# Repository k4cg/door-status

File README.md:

# K4CG door-status

This program submits the k4cg space door status to "heimat". It is intended to run on an ESP8266 controller with micropython firmware. In the "hardware" directory, you can find a case design for OpenSCAD, which is suitable for 3D-printing.

[Link: Miropython ESP8266 Docs](http://docs.micropython.org/en/latest/esp8266/)

## Status Transmission

The data transfer is periodically performed by the ESP (~ 5 minute intervals) to http://heimat:8000 via PUT request.

It contains a JSON formatted structure like:
```
{"humidity": 35, "door": "open", "date": "2017-08-21 19:11:50", "tempDoor": 27}
```

## Code Upload

First time upload: Connect via serial port with mpfshell:

```
# mpfshell -c "open ttyUSB0"
mpfs [/]> put boot.py
mpfs [/]> put service.py
...
```

Update code:
```
# mpfshell -c "open ws:192.168.178.9,PASSWORD"
mpfs [/]> put boot.py
mpfs [/]> put service.py
...
mpfs [/]> repl
>>> reboot()
```

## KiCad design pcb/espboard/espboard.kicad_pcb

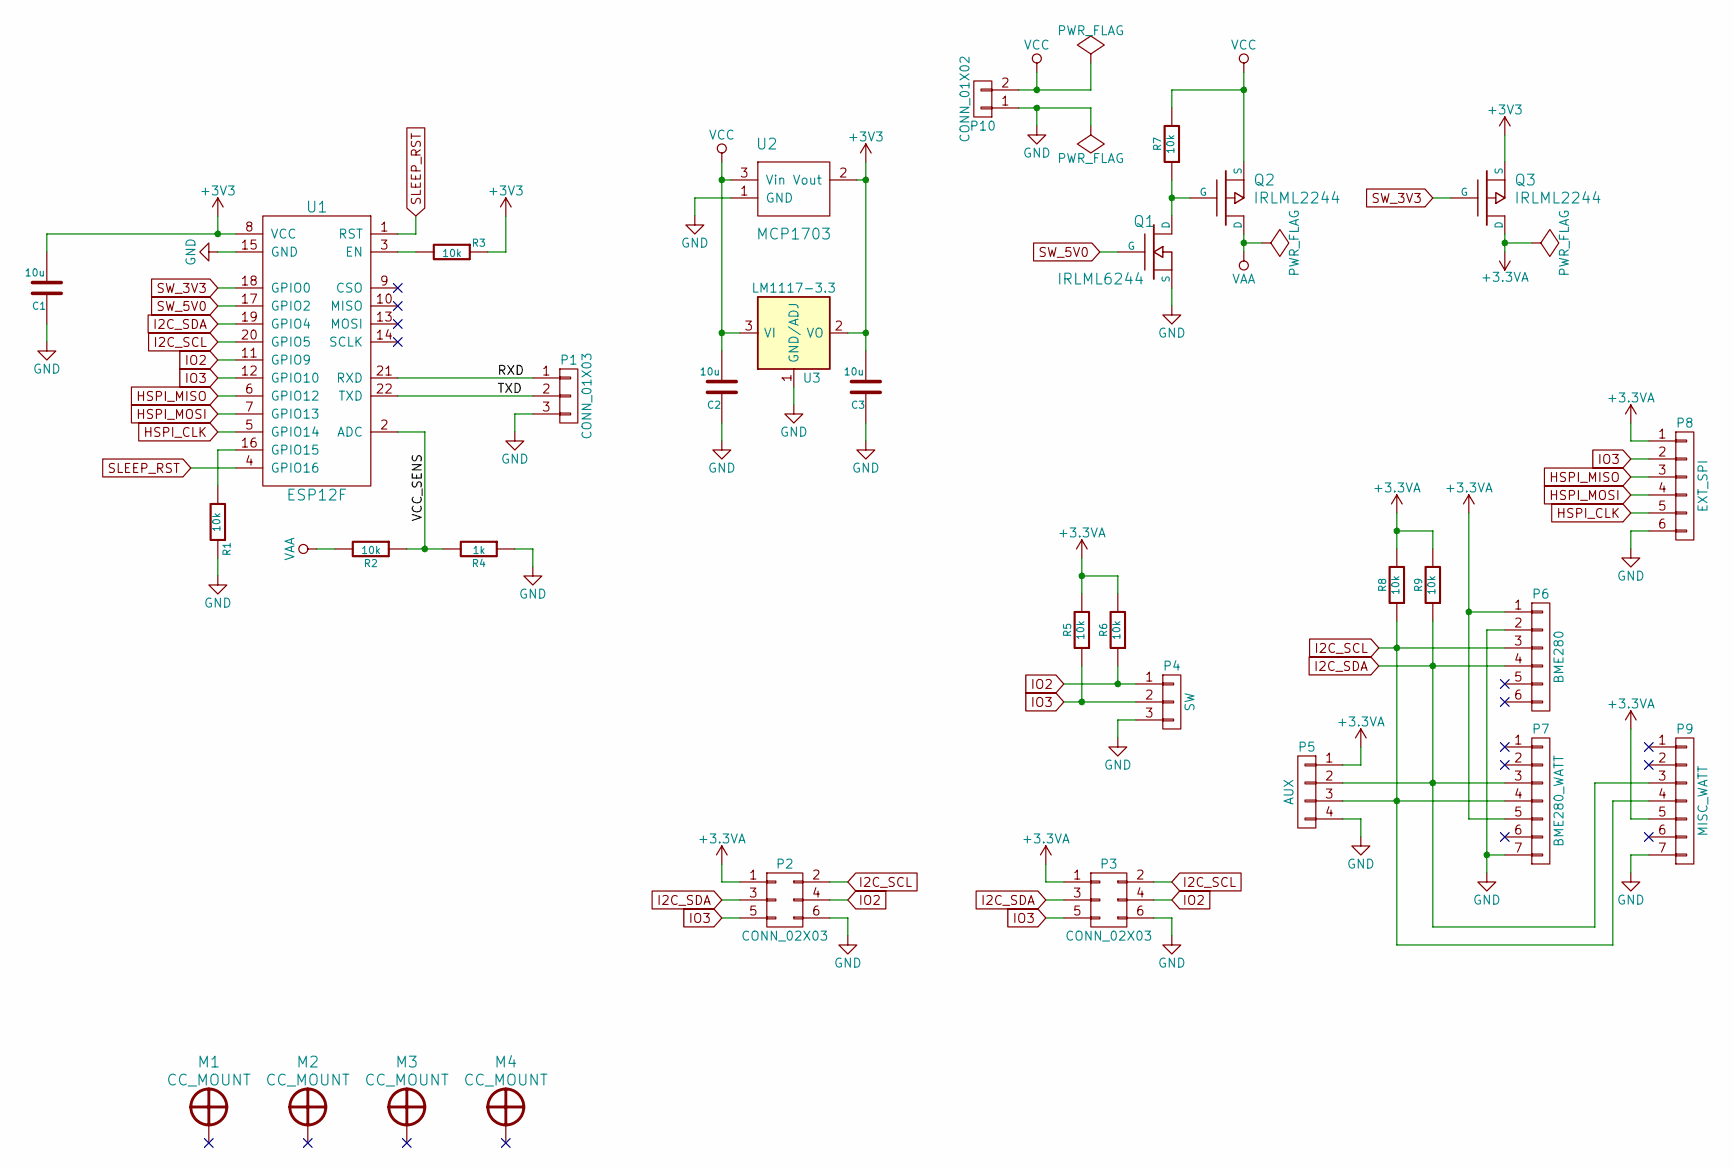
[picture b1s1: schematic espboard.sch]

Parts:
C1, C2, C3: 10u; rcl-cc-0402
M1, M2, M3, M4: CC_MOUNT; CC_MOUNT_PLATED_M3
P1: CONN_01X03; Pin_Header_Straight_1x03_Pitch2.54mm
P2, P3: CONN_02X03; con-harting-ml-ML6
P4: SW; Pin_Header_Straight_1x03_Pitch2.54mm
P5: AUX; Pin_Header_Straight_1x04_Pitch2.54mm
P6: BME280; Pin_Header_Straight_1x06_Pitch2.54mm
P7: BME280_WATT; Pin_Header_Straight_1x07_Pitch2.54mm
P8: EXT_SPI; Pin_Header_Straight_1x06_Pitch2.54mm
P9: MISC_WATT; Pin_Header_Straight_1x07_Pitch2.54mm
P10: CONN_01X02; Pin_Header_Straight_1x02_Pitch2.54mm
Q1: IRLML6244; CC_SOT23_MOS1
Q2, Q3: IRLML2244; CC_SOT23_MOS1
R1, R2, R3, R5, R6, R7, R8, R9: 10k; rcl-cc-0402
R4: 1k; rcl-cc-0402
U1: ESP12F; esp12f
U2: MCP1703; SOT-89-3_Handsoldering
U3: LM1117-3.3; SOT-223

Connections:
+3.3VA: P2.1, P3.1, P5.1, P6.1, P7.5, P8.1, P9.5, Q3.D, R5.2, R6.2, R8.2, R9.2
+3V3: C1.2, C3.2, Q3.S, R3.1, U1.8 (VCC), U2.2 (Vout), U3.2 (VO), U3.4 (VO)
/RXD: P1.1, U1.21 (RXD)
/TXD: P1.2, U1.22 (TXD)
/VCC_SENS: R2.1, R4.2, U1.2 (ADC)
GND: C1.1, C2.1, C3.1, P1.3, P2.6, P3.6, P4.3, P5.4, P6.2, P7.7, P8.6, P9.7, P10.1, Q1.S, R1.1, R4.1, U1.15 (GND), U2.1 (GND), U3.1 (GND/ADJ)
HSPI_CLK: P8.5, U1.5 (GPIO14)
HSPI_MISO: P8.3, U1.6 (GPIO12)
HSPI_MOSI: P8.4, U1.7 (GPIO13)
I2C_SCL: P2.2, P3.2, P5.3, P6.3, P7.4, P9.4, R8.1, U1.20 (GPIO5)
I2C_SDA: P2.3, P3.3, P5.2, P6.4, P7.3, P9.3, R9.1, U1.19 (GPIO4)
IO2: P2.4, P3.4, P4.1, R6.1, U1.11 (GPIO9)
IO3: P2.5, P3.5, P4.2, P8.2, R5.1, U1.12 (GPIO10)
unnamed: Q1.D, Q2.G, R7.1
unnamed: R1.2, U1.16 (GPIO15)
unnamed: R3.2, U1.3 (EN)
SLEEP_RST: U1.1 (RST), U1.4 (GPIO16)
SW_3V3: Q3.G, U1.18 (GPIO0)
SW_5V0: Q1.G, U1.17 (GPIO2)
VAA: Q2.D, R2.2
VCC: C2.2, P10.2, Q2.S, R7.2, U2.3 (Vin), U3.3 (VI)

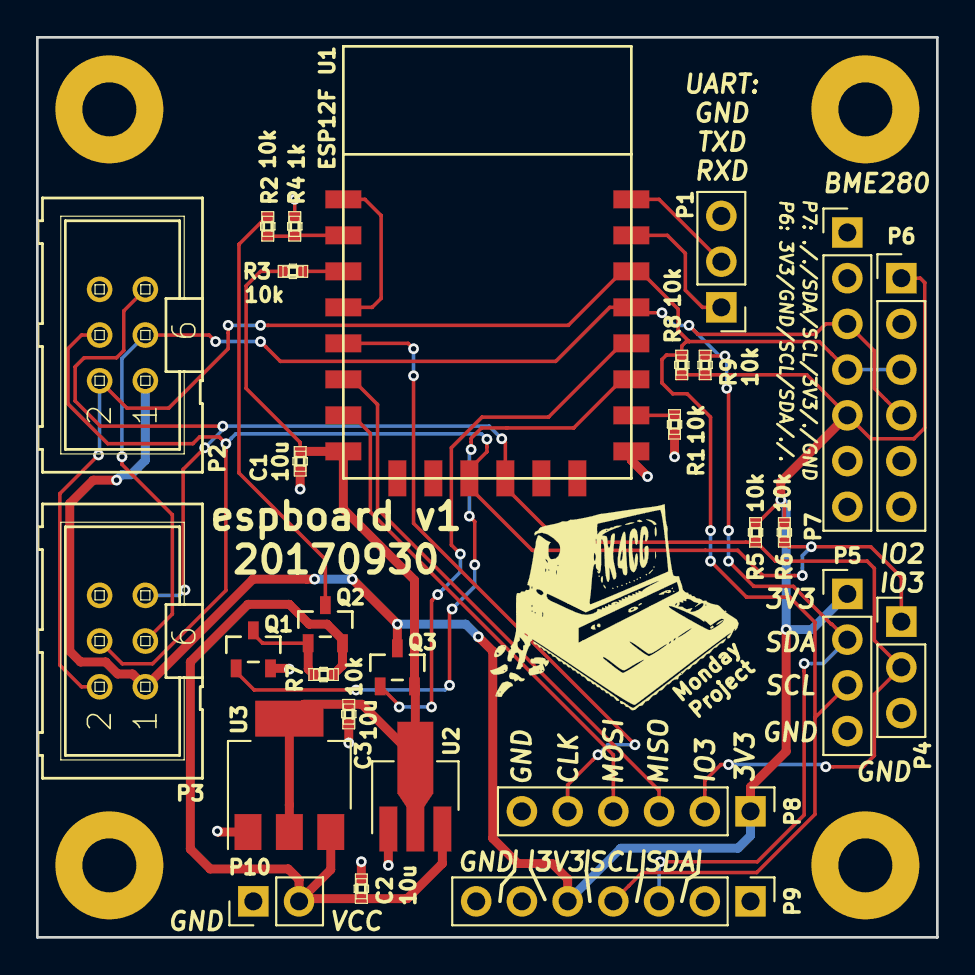
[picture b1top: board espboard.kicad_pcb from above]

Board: 2 copper layers, 50.0 x 50.0 mm, 32 parts (0 on the bottom side), 21 nets.

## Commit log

2017-08-21 initial code upload
2017-08-23 added openscad files for case 3d printing, updated and fixed readme
2017-08-24 catch all exceptions, ensure deepsleep after exception
2017-08-24 changed date format, added time zone in label for reference
2017-09-09 refactored using json based configuration file, removed exception catch
2017-09-09 added watchdog timer, moved some timing values to json config
2017-09-11 use internal pullup for door switch
2017-09-11 added mqtt push
2017-09-14 fixed bug in door status setting
2017-09-30 moved case to 'case' folder
2017-09-30 added pcb
2017-11-06 added mqtt service configuration for multiple targets
2017-11-06 removed leading slashes in mqtt topics in config template
2017-11-18 updated case for pcb
2017-11-27 removed dht11
2017-11-27 added power config, added i2c and bme280
2017-11-27 implemented service handling for sensor config lists
2017-11-27 updated config template
2017-12-07 make http push less critical, fixed bug
2018-01-04 added timestamp to json dump
2018-03-15 always publish json structures on mqtt
2018-09-24 feature: don't publish retained messages
2019-03-25 added p5 sensor mechanism
2022-07-17 make mqtt values numeric for influxdb

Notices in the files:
pcb/espboard/espboard.kicad_pcb:
license: GPLv3 or any later version
